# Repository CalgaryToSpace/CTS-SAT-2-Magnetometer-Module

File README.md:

# CTS-SAT-2-Magnetometer-Module

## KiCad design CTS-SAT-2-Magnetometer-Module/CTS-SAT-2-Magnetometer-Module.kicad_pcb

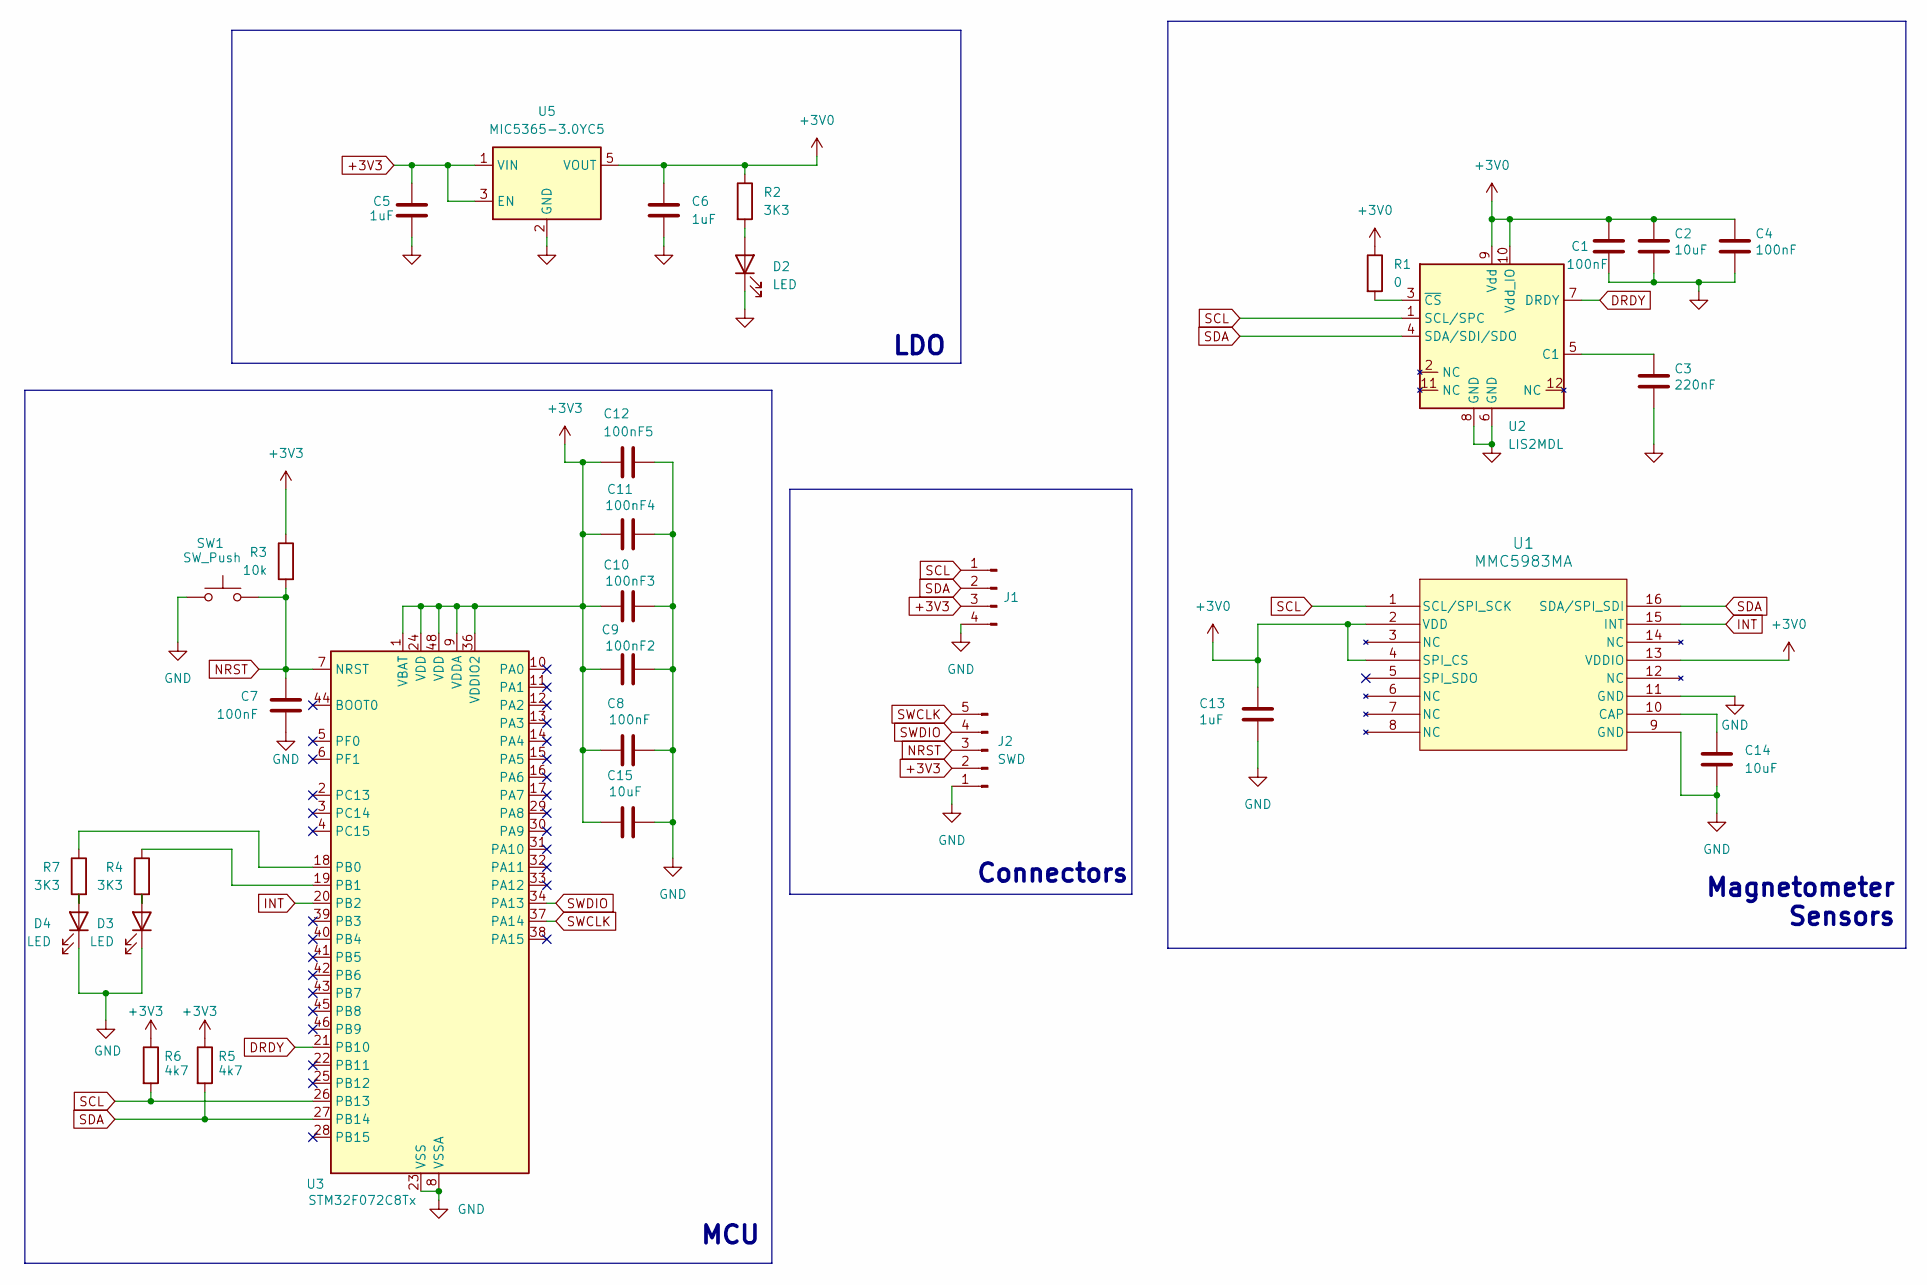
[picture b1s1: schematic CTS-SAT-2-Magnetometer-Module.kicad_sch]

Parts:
C1, C4, C7, C8: 100nF; C_0603_1608Metric_Pad1.08x0.95mm_HandSolder
C2: 10uF; C_1206_3216Metric_Pad1.33x1.80mm_HandSolder
C3: 220nF; C_0603_1608Metric_Pad1.08x0.95mm_HandSolder
C5, C6, C13: 1uF; C_0603_1608Metric_Pad1.08x0.95mm_HandSolder
C9: 100nF2; C_0603_1608Metric_Pad1.08x0.95mm_HandSolder
C10: 100nF3; C_0603_1608Metric_Pad1.08x0.95mm_HandSolder
C11: 100nF4; C_0603_1608Metric_Pad1.08x0.95mm_HandSolder
C12: 100nF5; C_0603_1608Metric_Pad1.08x0.95mm_HandSolder
C14, C15: 10uF; C_0603_1608Metric_Pad1.08x0.95mm_HandSolder
D2, D3, D4: LED; LED_0603_1608Metric_Pad1.05x0.95mm_HandSolder
J1: Conn_01x04_Pin; PinHeader_1x04_P2.54mm_Vertical
J2: SWD; PinSocket_1x05_P2.54mm_Vertical
R1: 0; R_0603_1608Metric_Pad0.98x0.95mm_HandSolder
R2, R4, R7: 3K3; R_0603_1608Metric_Pad0.98x0.95mm_HandSolder
R3: 10k; R_0603_1608Metric_Pad0.98x0.95mm_HandSolder
R5, R6: 4k7; R_0603_1608Metric_Pad0.98x0.95mm_HandSolder
SW1: SW_Push; SW_SPST_EVQP0
U1: MMC5983MA; MMC5983MA_MEM
U2: LIS2MDL; LGA-12_2x2mm_P0.5mm
U3: STM32F072C8Tx; LQFP-48_7x7mm_P0.5mm
U5: MIC5365-3.0YC5; SOT-353_SC-70-5

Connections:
+3V0: C1.2, C2.1, C4.1, C6.1, C13.1, R1.1, R2.1, U1.2 (VDD), U1.4 (SPI_CS), U1.13 (VDDIO), U2.9 (Vdd), U2.10 (Vdd_IO), U5.5 (VOUT)
+3V3: C5.1, C8.2, C9.2, C10.1, C11.2, C12.1, C15.2, J1.3, J2.2, R3.1, R5.1, R6.1, U3.1 (VBAT), U3.9 (VDDA), U3.24 (VDD), U3.36 (VDDIO2), U3.48 (VDD), U5.1 (VIN), U5.3 (EN)
DRDY: U2.7 (DRDY), U3.21 (PB10)
GND: C1.1, C2.2, C3.2, C4.2, C5.2, C6.2, C7.2, C8.1, C9.1, C10.2, C11.1, C12.2, C13.2, C14.2, C15.1, D2.1 (K), D3.1 (K), D4.1 (K), J1.4, J2.1, SW1.2, U1.9 (GND), U1.11 (GND), U2.6 (GND), U2.8 (GND), U3.8 (VSSA), U3.23 (VSS), U3.35 (VSS), U3.47 (VSS), U5.2 (GND)
INT: U1.15 (INT), U3.20 (PB2)
NRST: C7.1, J2.3, R3.2, SW1.1, U3.7 (NRST)
unnamed: D2.2 (A), R2.2
unnamed: D3.2 (A), R4.2
unnamed: D4.2 (A), R7.2
unnamed: C14.1, U1.10 (CAP)
unnamed: C3.1, U2.5 (C1)
unnamed: R1.2, U2.3 (~CS)
unnamed: R7.1, U3.18 (PB0)
unnamed: R4.1, U3.19 (PB1)
SCL: J1.1, R6.2, U1.1 (SCL/SPI_SCK), U2.1 (SCL/SPC), U3.26 (PB13)
SDA: J1.2, R5.2, U1.16 (SDA/SPI_SDI), U2.4 (SDA/SDI/SDO), U3.27 (PB14)
SWCLK: J2.5, U3.37 (PA14)
SWDIO: J2.4, U3.34 (PA13)

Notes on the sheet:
Connectors
LDO
MCU
Magnetometer Sensors

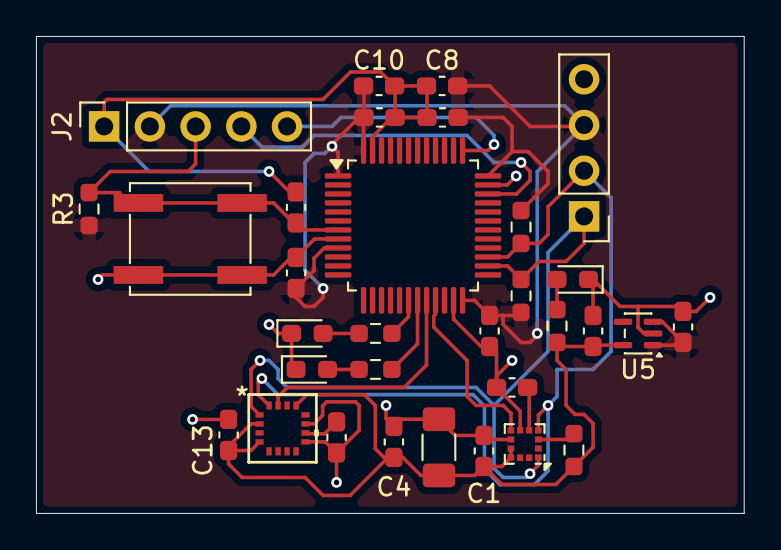
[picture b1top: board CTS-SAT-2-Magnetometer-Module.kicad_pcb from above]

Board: 6 copper layers, 39.3 x 26.5 mm, 32 parts (0 on the bottom side), 18 nets.

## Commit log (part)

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2026-02-21 V1 of the schematic
    Started the schematic
2026-03-03 Updated Schematic and Started Layout
    Assigned Footprints and Started PCB layout
2026-04-11 Started PCB Routing
    Still need to figure out how to do routing for communication lines
2026-06-06 PCB Completed with Labels
2026-06-06 Changed one of the footprints
2026-06-27 Few first edits
2026-06-27 Aaryan's Changes applied
2026-06-27 Final changes for Aaryan
